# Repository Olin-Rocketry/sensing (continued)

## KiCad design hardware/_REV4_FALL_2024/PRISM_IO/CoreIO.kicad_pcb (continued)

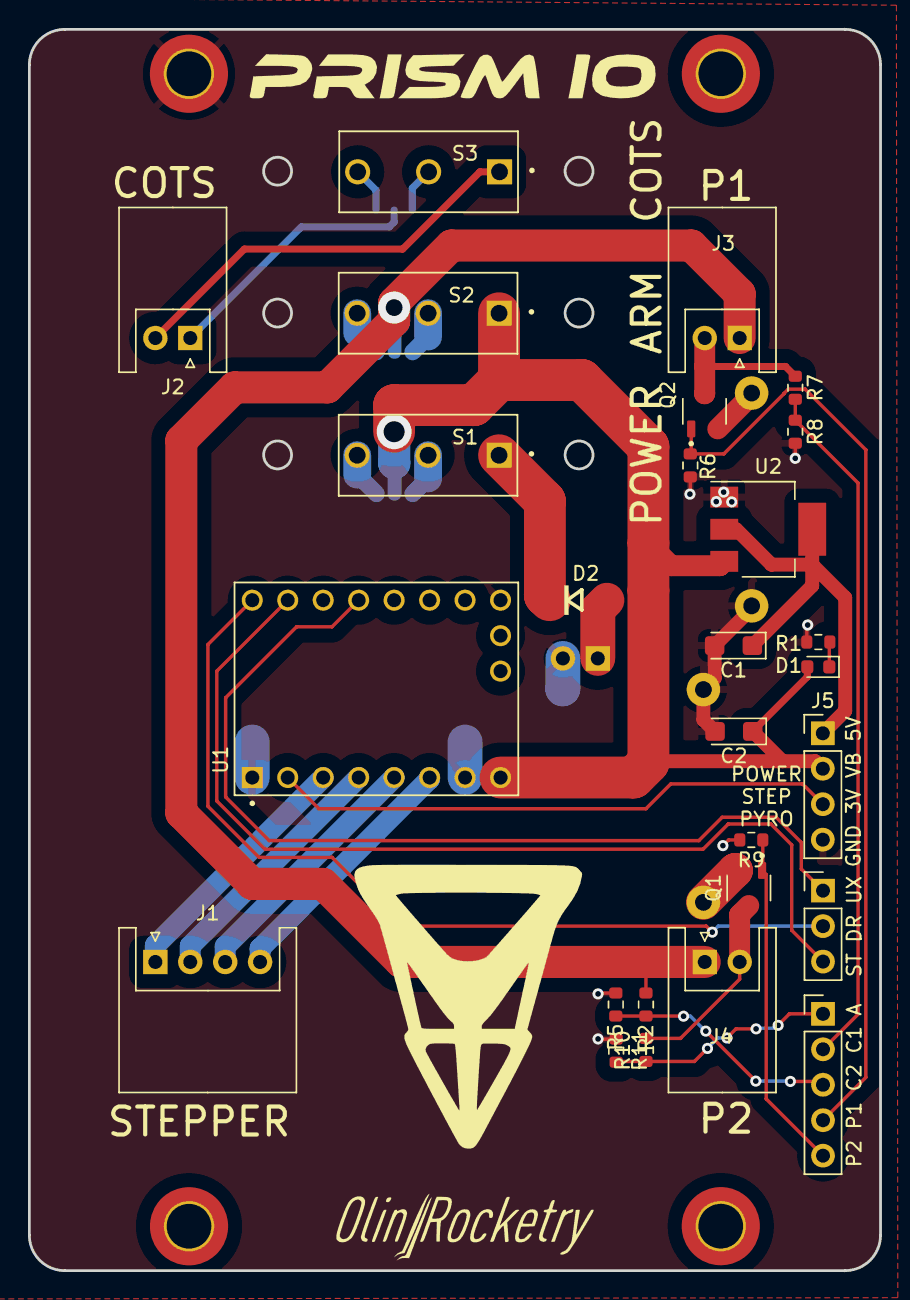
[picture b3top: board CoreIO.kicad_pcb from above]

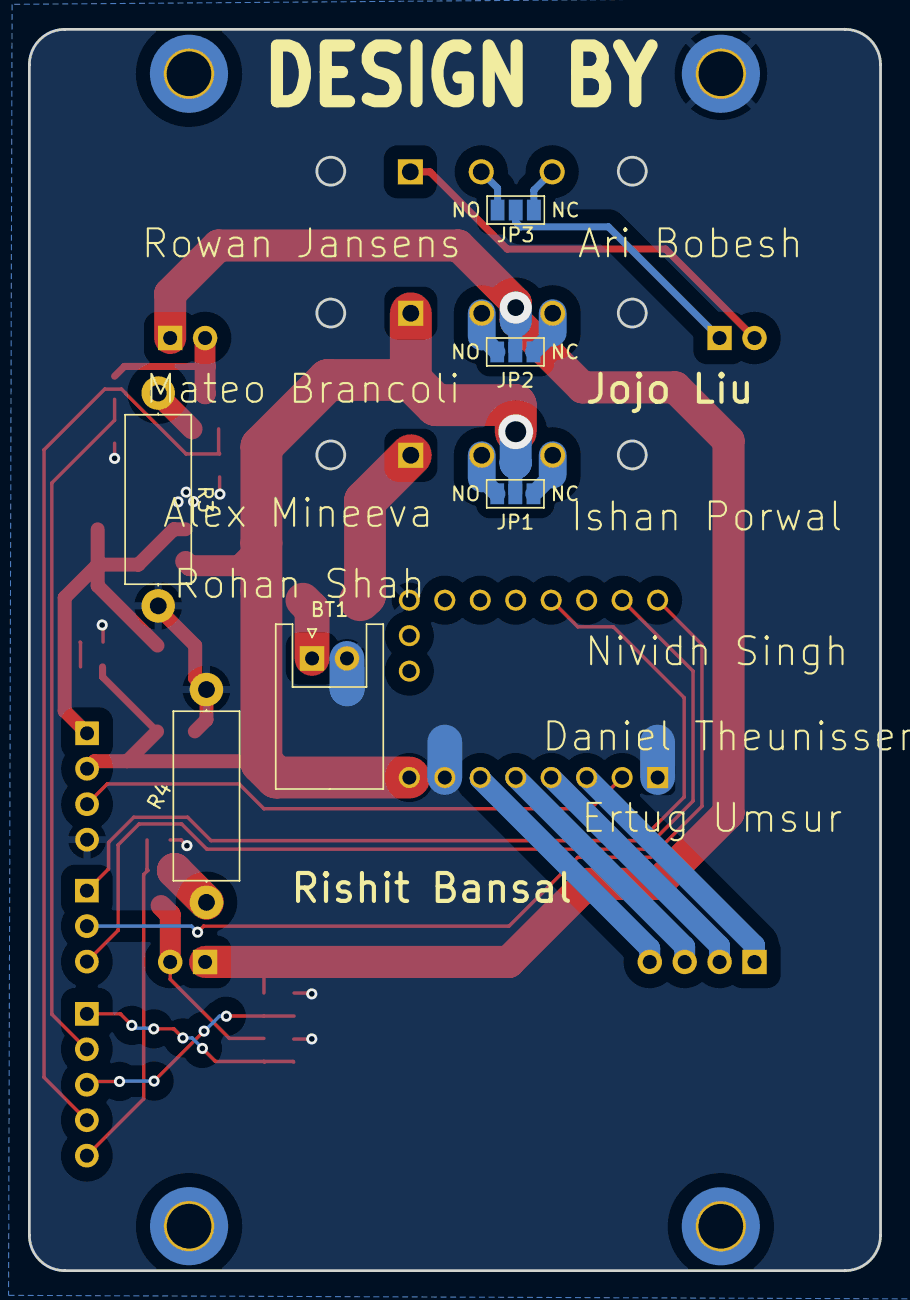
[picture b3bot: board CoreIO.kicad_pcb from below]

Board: 2 copper layers, 61.0 x 88.9 mm, 37 parts (6 on the bottom side), 32 nets.

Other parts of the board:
Pyro2: Conn_01x05_Socket; PinHeader_1x05_P2.54mm_Vertical
Stepper2: Conn_01x03_Socket; PinHeader_1x03_P2.54mm_Vertical

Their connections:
/ARM: Pyro2.3; also elsewhere on the board
/CONT 1: Pyro2.2; also elsewhere on the board
/CONT 2: Pyro2.1; also elsewhere on the board
/DIR: Stepper2.2; also elsewhere on the board
/PYRO 1: Pyro2.4; also elsewhere on the board
/PYRO 2: Pyro2.5; also elsewhere on the board
/STEP: Stepper2.3; also elsewhere on the board
/UART: Stepper2.1; also elsewhere on the board

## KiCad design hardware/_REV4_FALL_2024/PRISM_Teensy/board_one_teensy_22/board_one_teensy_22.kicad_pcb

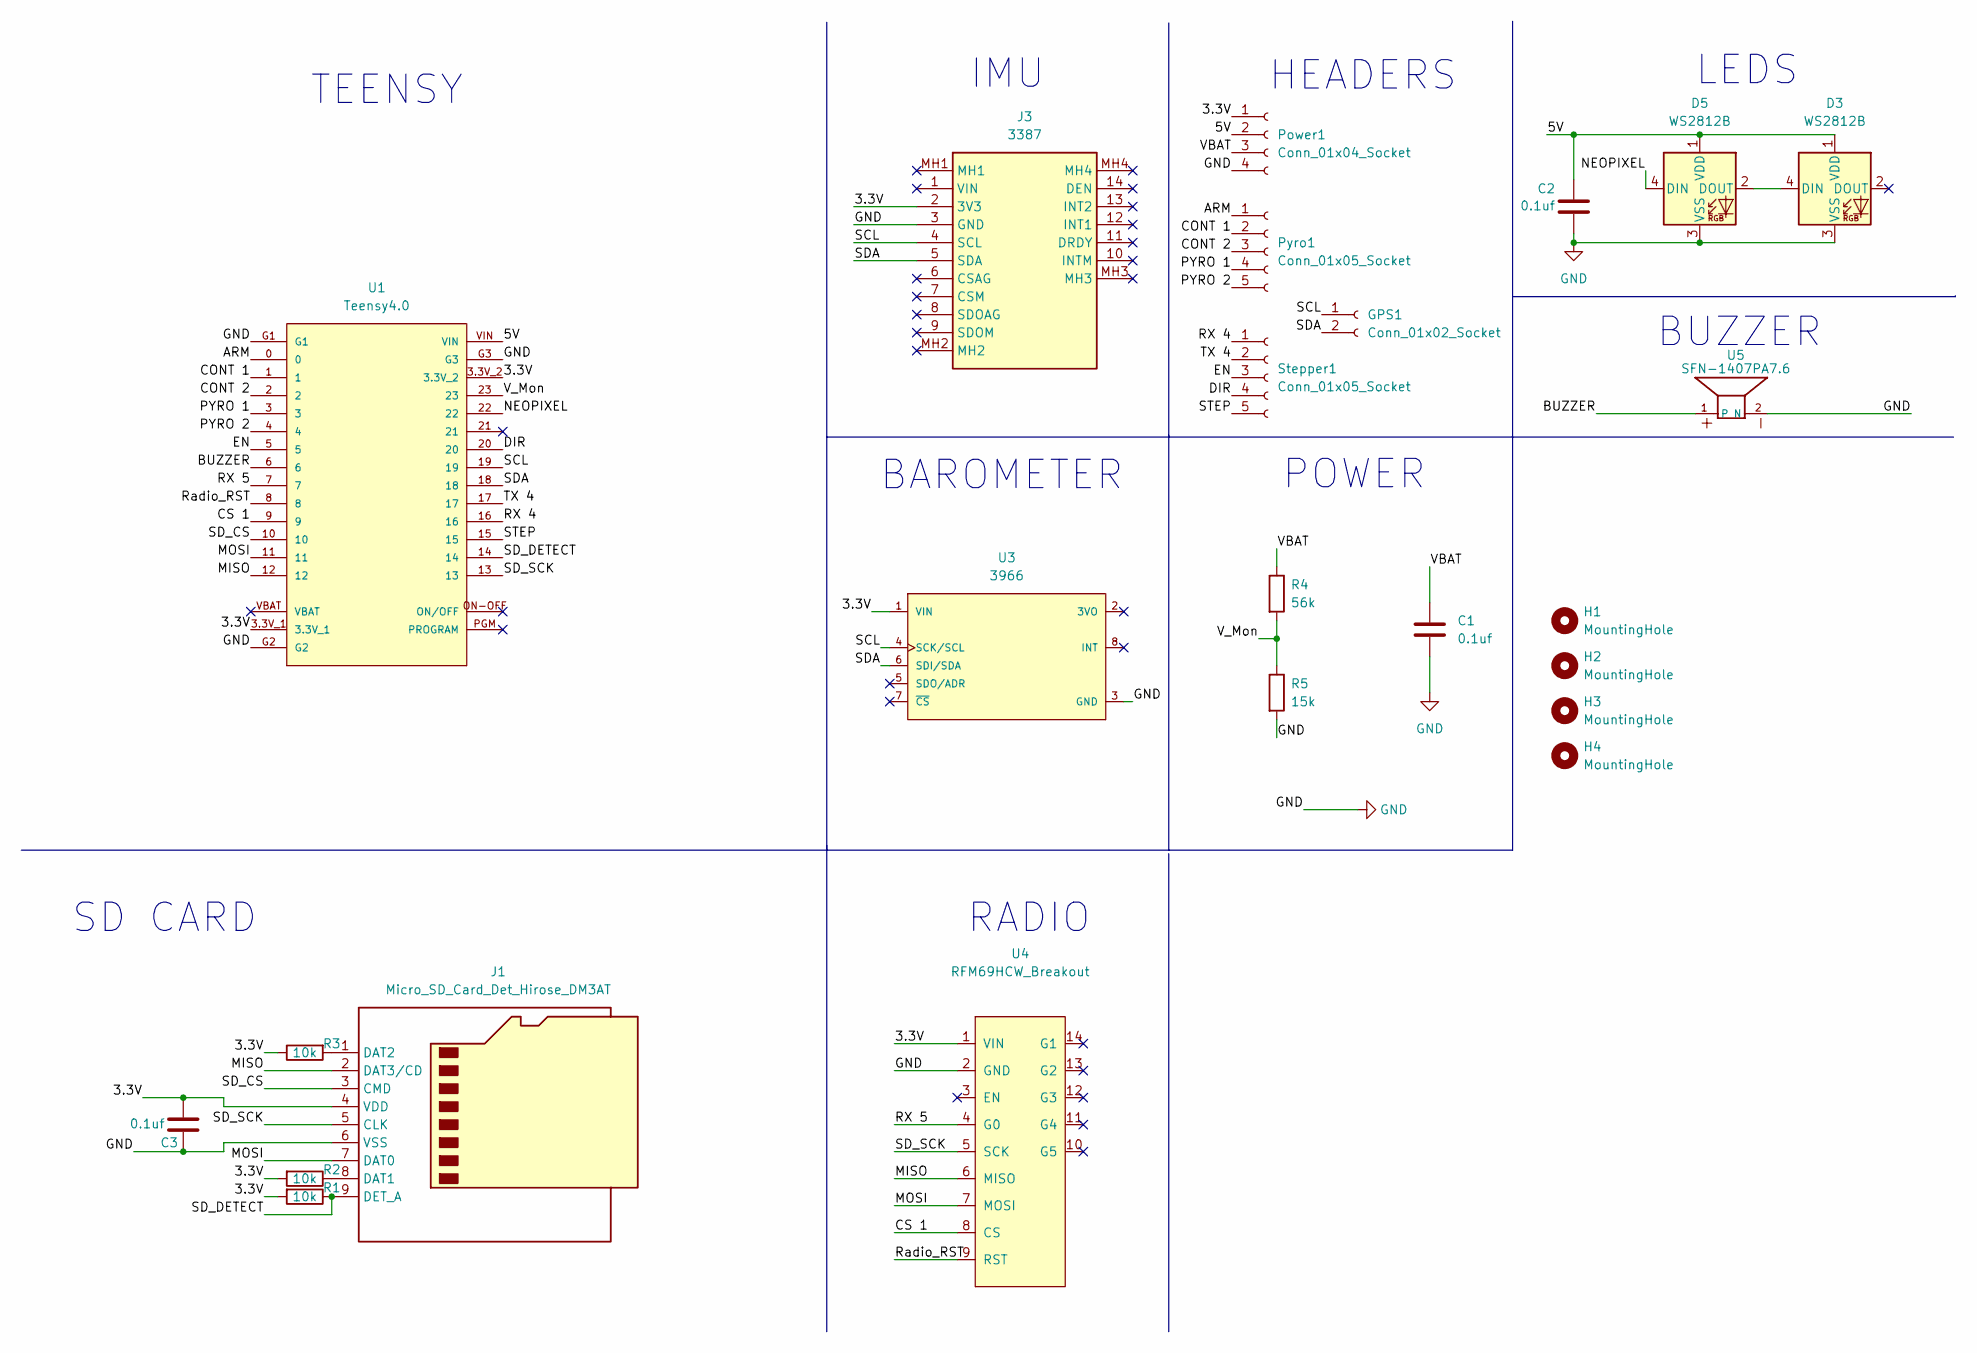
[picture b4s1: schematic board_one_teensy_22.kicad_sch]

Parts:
C1, C2, C3: 0.1uf; C_0603_1608Metric
D3, D5: WS2812B
GPS1: Conn_01x02_Socket; PinHeader_1x02_P2.54mm_Vertical
H1, H2, H3, H4: MountingHole; MountingHole_3.2mm_M3_DIN965_Pad_TopBottom
J1: Micro_SD_Card_Det_Hirose_DM3AT; HRS_DM3CS-SF
J3: 3387; Manufacturer_Part_Number 3387
Power1: Conn_01x04_Socket; PinHeader_1x04_P2.54mm_Vertical
Pyro1: Conn_01x05_Socket; PinHeader_1x05_P2.54mm_Vertical
R1, R2, R3: 10k; R_0603_1608Metric
R4: 56k; R_0603_1608Metric
R5: 15k; R_0603_1608Metric
Stepper1: Conn_01x05_Socket; PinHeader_1x05_P2.54mm_Vertical
U1: Teensy4.0; MODULE_DEV-15583
U3: 3966; Adafruit_Industries-3966-MFG; mouser part number 485-3966; digikey description BMP388 - PRECISION BAROMETRIC PR
U4: RFM69HCW_Breakout
U5: SFN-1407PA7.6; PARTREV 31/03/20

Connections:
/3.3V: C3.2, J1.4 (VDD), J3.2 (3V3), Power1.1, R1.2, R2.2, R3.1, U1.3.3V_1, U1.3.3V_2, U3.1 (VIN), U4.1 (VIN)
/5V: C2.2, D3.1 (VDD), D5.1 (VDD), Power1.2, U1.VIN
/ARM: Pyro1.1, U1.0
/BUZZER: U1.6, U5.1
/CONT 1: Pyro1.2, U1.1
/CONT 2: Pyro1.3, U1.2
/CS 1: U1.9, U4.8 (CS)
/DIR: Stepper1.4, U1.20
/EN: Stepper1.3, U1.5
/MISO: J1.2 (DAT3/CD), U1.12, U4.6 (MISO)
/MOSI: J1.7 (DAT0), U1.11, U4.7 (MOSI)
/NEOPIXEL: D5.4 (DIN), U1.22
/PYRO 1: Pyro1.4, U1.3
/PYRO 2: Pyro1.5, U1.4
/RX 4: Stepper1.1, U1.16
/RX 5: U1.7, U4.4 (G0)
/Radio_RST: U1.8, U4.9 (RST)
/SCL: GPS1.1, J3.4 (SCL), U1.19, U3.4 (SCK/SCL)
/SDA: GPS1.2, J3.5 (SDA), U1.18, U3.6 (SDI/SDA)
/SD_CS: J1.3 (CMD), U1.10
/SD_DETECT: J1.9 (DET_A), R1.1, U1.14
/SD_SCK: J1.5 (CLK), U1.13, U4.5 (SCK)
/STEP: Stepper1.5, U1.15
/TX 4: Stepper1.2, U1.17
/VBAT: C1.1, Power1.3, R4.1
/V_Mon: R4.2, R5.1, U1.23
GND: C1.2, C2.1, C3.1, D3.3 (VSS), D5.3 (VSS), J1.6 (VSS), J3.3 (GND), Power1.4, R5.2, U1.G1, U1.G2, U1.G3, U3.3 (GND), U4.2 (GND), U5.2 (N)
unnamed: D3.4 (DIN), D5.2 (DOUT)
unnamed: J1.8 (DAT1), R2.1
unnamed: J1.1 (DAT2), R3.2

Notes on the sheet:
BUZZER
TEENSY
HEADERS
SD CARD
POWER
LEDS
IMU
BAROMETER
RADIO

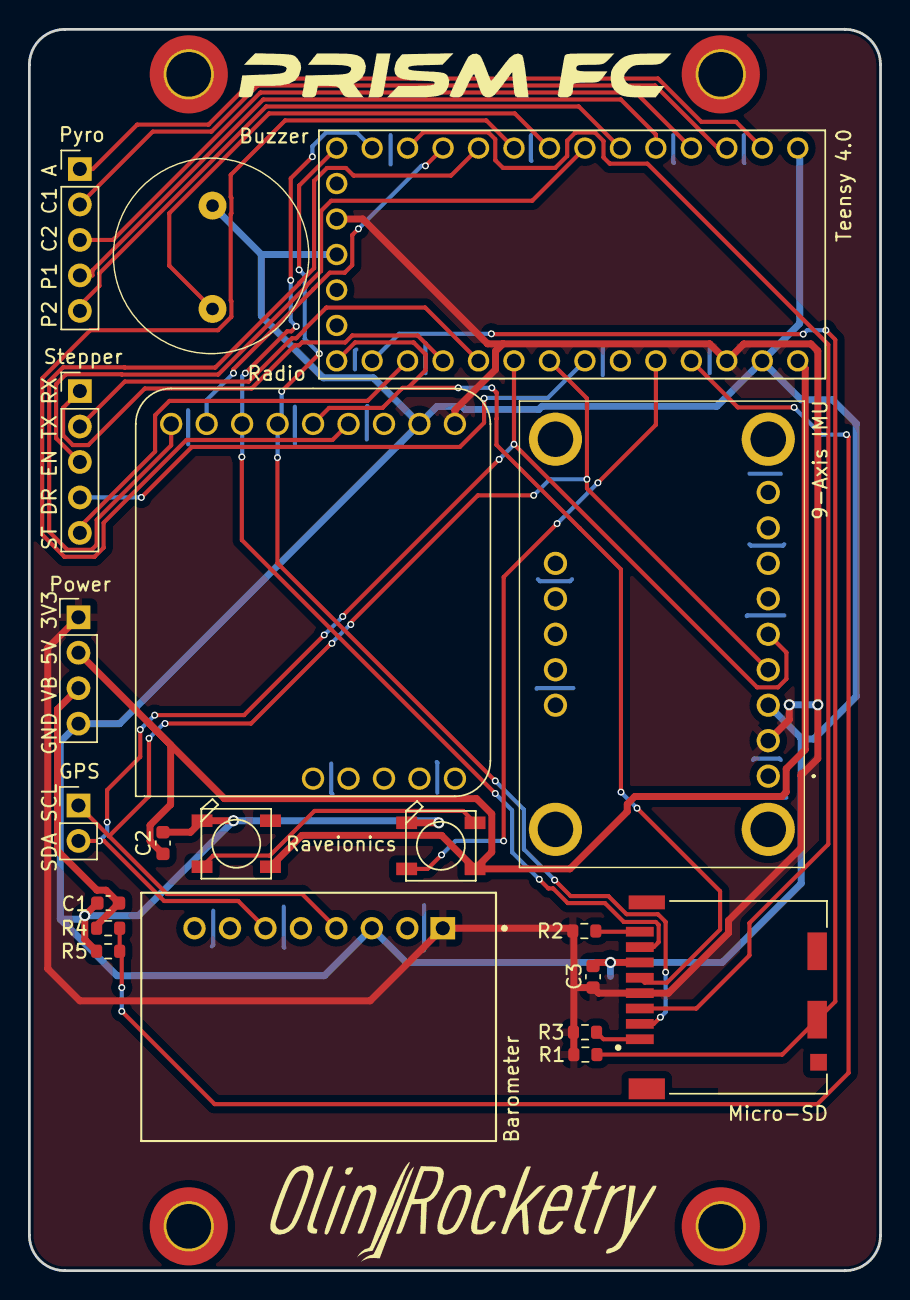
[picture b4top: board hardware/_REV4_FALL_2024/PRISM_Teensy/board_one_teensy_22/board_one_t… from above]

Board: 2 copper layers, 61.0 x 88.9 mm, 24 parts (0 on the bottom side), 30 nets.

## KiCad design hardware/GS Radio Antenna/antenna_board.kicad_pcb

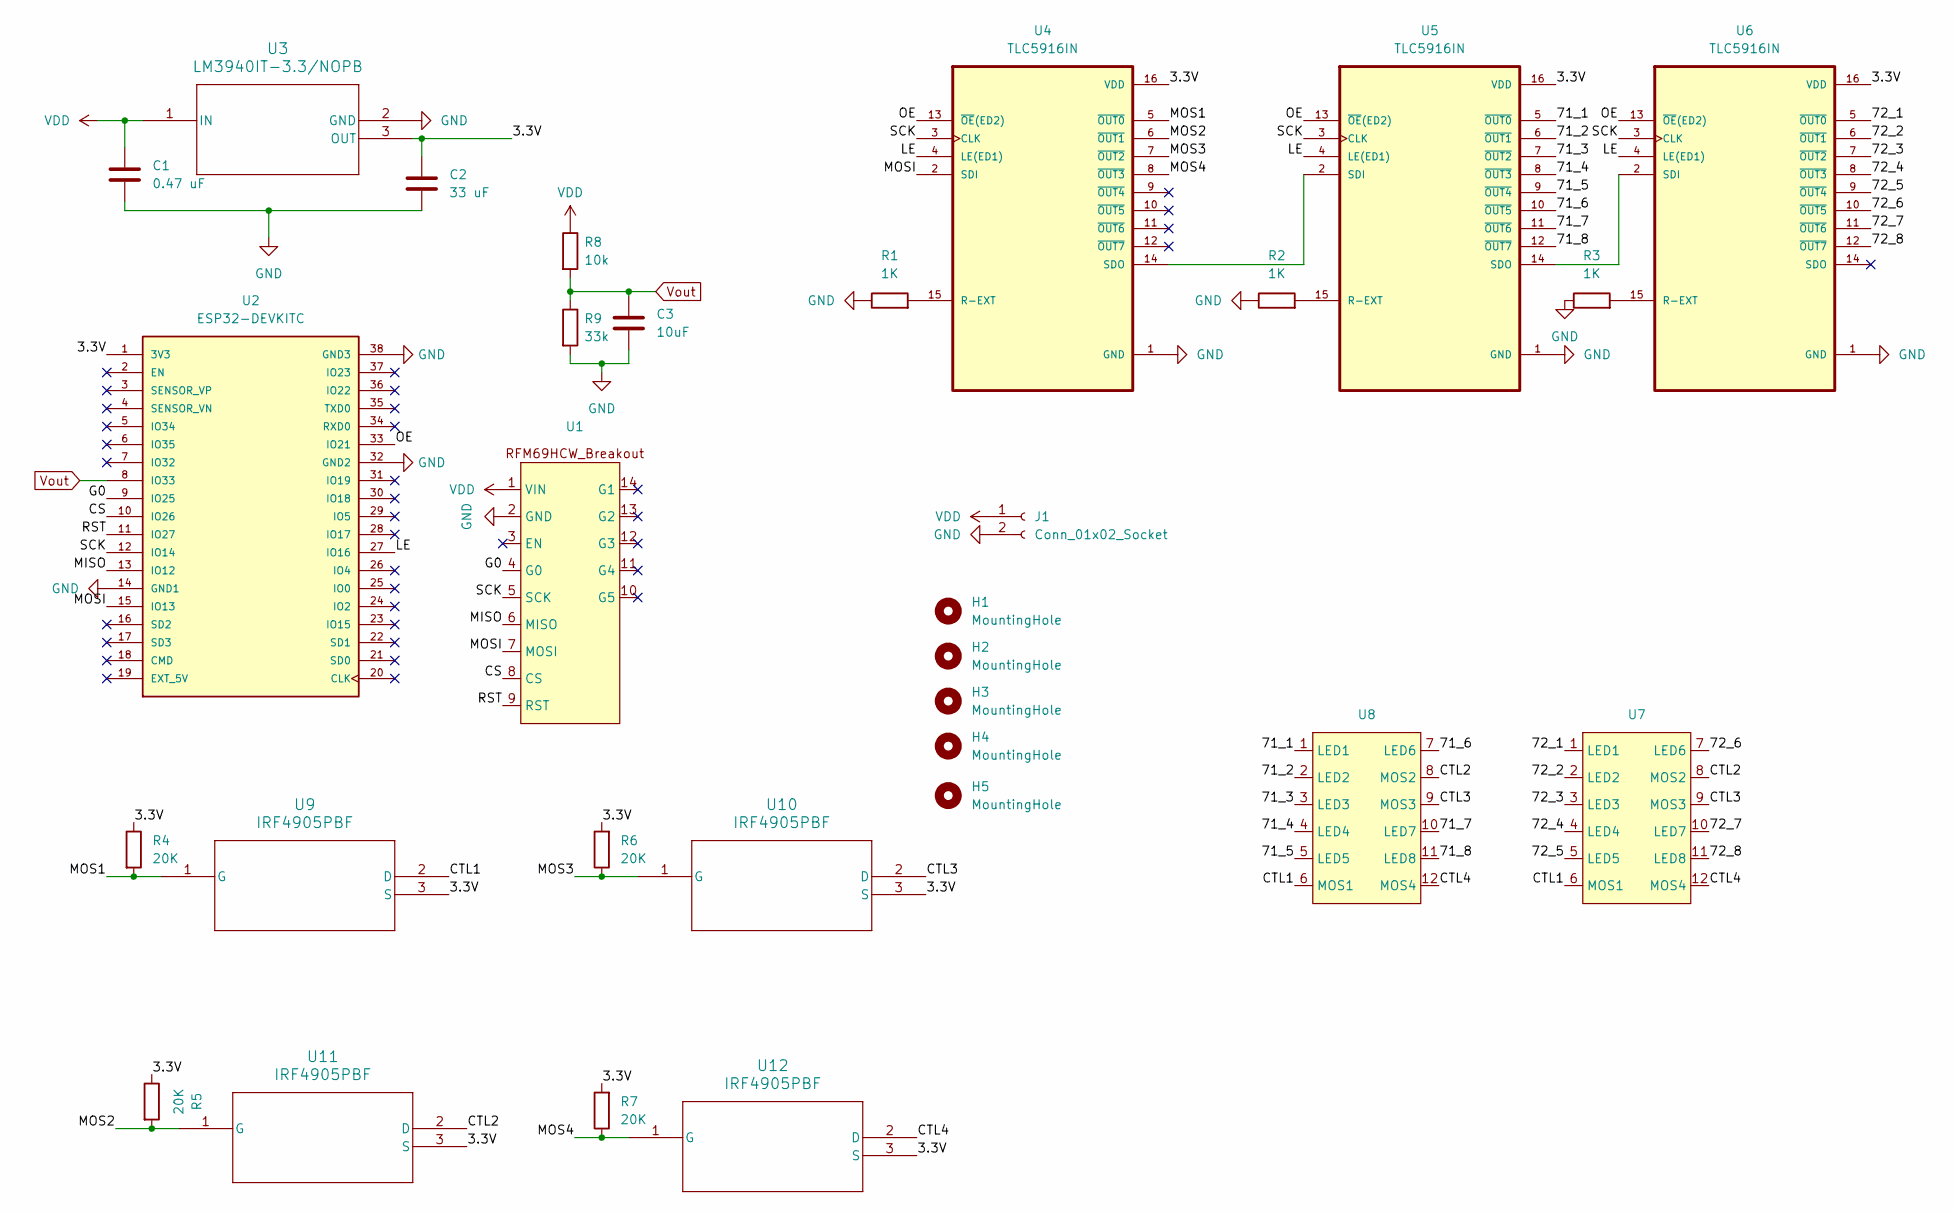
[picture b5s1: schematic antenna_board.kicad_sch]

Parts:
C1: 0.47 uF; C_0603_1608Metric_Pad1.08x0.95mm_HandSolder
C2: 33 uF; C_0805_2012Metric_Pad1.18x1.45mm_HandSolder
C3: 10uF; C_0603_1608Metric_Pad1.08x0.95mm_HandSolder
H1, H2, H3, H4, H5: MountingHole; MountingHole_3.2mm_M3_DIN965_Pad_TopBottom
J1: Conn_01x02_Socket; PinSocket_1x02_P2.54mm_Vertical
R1, R2, R3: 1K; R_0603_1608Metric_Pad0.98x0.95mm_HandSolder
R4, R5, R6, R7: 20K; R_0603_1608Metric_Pad0.98x0.95mm_HandSolder
R8: 10k; R_0603_1608Metric_Pad0.98x0.95mm_HandSolder
R9: 33k; R_0603_1608Metric_Pad0.98x0.95mm_HandSolder
U1: RFM69HCW_Breakout
U2: ESP32-DEVKITC; MODULE_ESP32-DEVKITC; PARTREV N/A
U3: LM3940IT-3.3/NOPB; LM3940IT
U4, U5, U6: TLC5916IN; DigiKey_Part_Number 296-24383-5-ND
U7, U8: Seven_Segment_Display
U9, U10, U11, U12: IRF4905PBF; PG-TO220-3_INF

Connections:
/3.3V: C2.1, R4.1, R5.1, R6.2, R7.2, U2.1 (3V3), U3.3 (OUT), U4.16 (VDD), U5.16 (VDD), U6.16 (VDD), U9.3 (S), U10.3 (S), U11.3 (S), U12.3 (S)
/71_1: U5.5 (~OUT0), U8.1 (LED1)
/71_2: U5.6 (~OUT1), U8.2 (LED2)
/71_3: U5.7 (~OUT2), U8.3 (LED3)
/71_4: U5.8 (~OUT3), U8.4 (LED4)
/71_5: U5.9 (~OUT4), U8.5 (LED5)
/71_6: U5.10 (~OUT5), U8.7 (LED6)
/71_7: U5.11 (~OUT6), U8.10 (LED7)
/71_8: U5.12 (~OUT7), U8.11 (LED8)
/72_1: U6.5 (~OUT0), U7.1 (LED1)
/72_2: U6.6 (~OUT1), U7.2 (LED2)
/72_3: U6.7 (~OUT2), U7.3 (LED3)
/72_4: U6.8 (~OUT3), U7.4 (LED4)
/72_5: U6.9 (~OUT4), U7.5 (LED5)
/72_6: U6.10 (~OUT5), U7.7 (LED6)
/72_7: U6.11 (~OUT6), U7.10 (LED7)
/72_8: U6.12 (~OUT7), U7.11 (LED8)
/CS: U1.8 (CS), U2.10 (IO26)
/CTL1: U7.6 (MOS1), U8.6 (MOS1), U9.2 (D)
/CTL2: U7.8 (MOS2), U8.8 (MOS2), U11.2 (D)
/CTL3: U7.9 (MOS3), U8.9 (MOS3), U10.2 (D)
/CTL4: U7.12 (MOS4), U8.12 (MOS4), U12.2 (D)
/G0: U1.4 (G0), U2.9 (IO25)
/LE: U2.27 (IO16), U4.4 (LE(ED1)), U5.4 (LE(ED1)), U6.4 (LE(ED1))
/MISO: U1.6 (MISO), U2.13 (IO12)
/MOS1: R4.2, U4.5 (~OUT0), U9.1 (G)
/MOS2: R5.2, U4.6 (~OUT1), U11.1 (G)
/MOS3: R6.1, U4.7 (~OUT2), U10.1 (G)
/MOS4: R7.1, U4.8 (~OUT3), U12.1 (G)
/MOSI: U1.7 (MOSI), U2.15 (IO13), U4.2 (SDI)
/OE: U2.33 (IO21), U4.13 (~OE(ED2)), U5.13 (~OE(ED2)), U6.13 (~OE(ED2))
/RST: U1.9 (RST), U2.11 (IO27)
/SCK: U1.5 (SCK), U2.12 (IO14), U4.3 (CLK), U5.3 (CLK), U6.3 (CLK)
GND: C1.2, C2.2, C3.2, J1.2, R1.1, R2.1, R3.1, R9.2, U1.2 (GND), U2.14 (GND1), U2.32 (GND2), U2.38 (GND3), U3.2 (GND), U4.1 (GND), U5.1 (GND), U6.1 (GND)
unnamed: R1.2, U4.15 (R-EXT)
unnamed: U4.14 (SDO), U5.2 (SDI)
unnamed: R2.2, U5.15 (R-EXT)
unnamed: U5.14 (SDO), U6.2 (SDI)
unnamed: R3.2, U6.15 (R-EXT)
VDD: C1.1, J1.1, R8.1, U1.1 (VIN), U3.1 (IN)
Vout: C3.1, R8.2, R9.1, U2.8 (IO33)

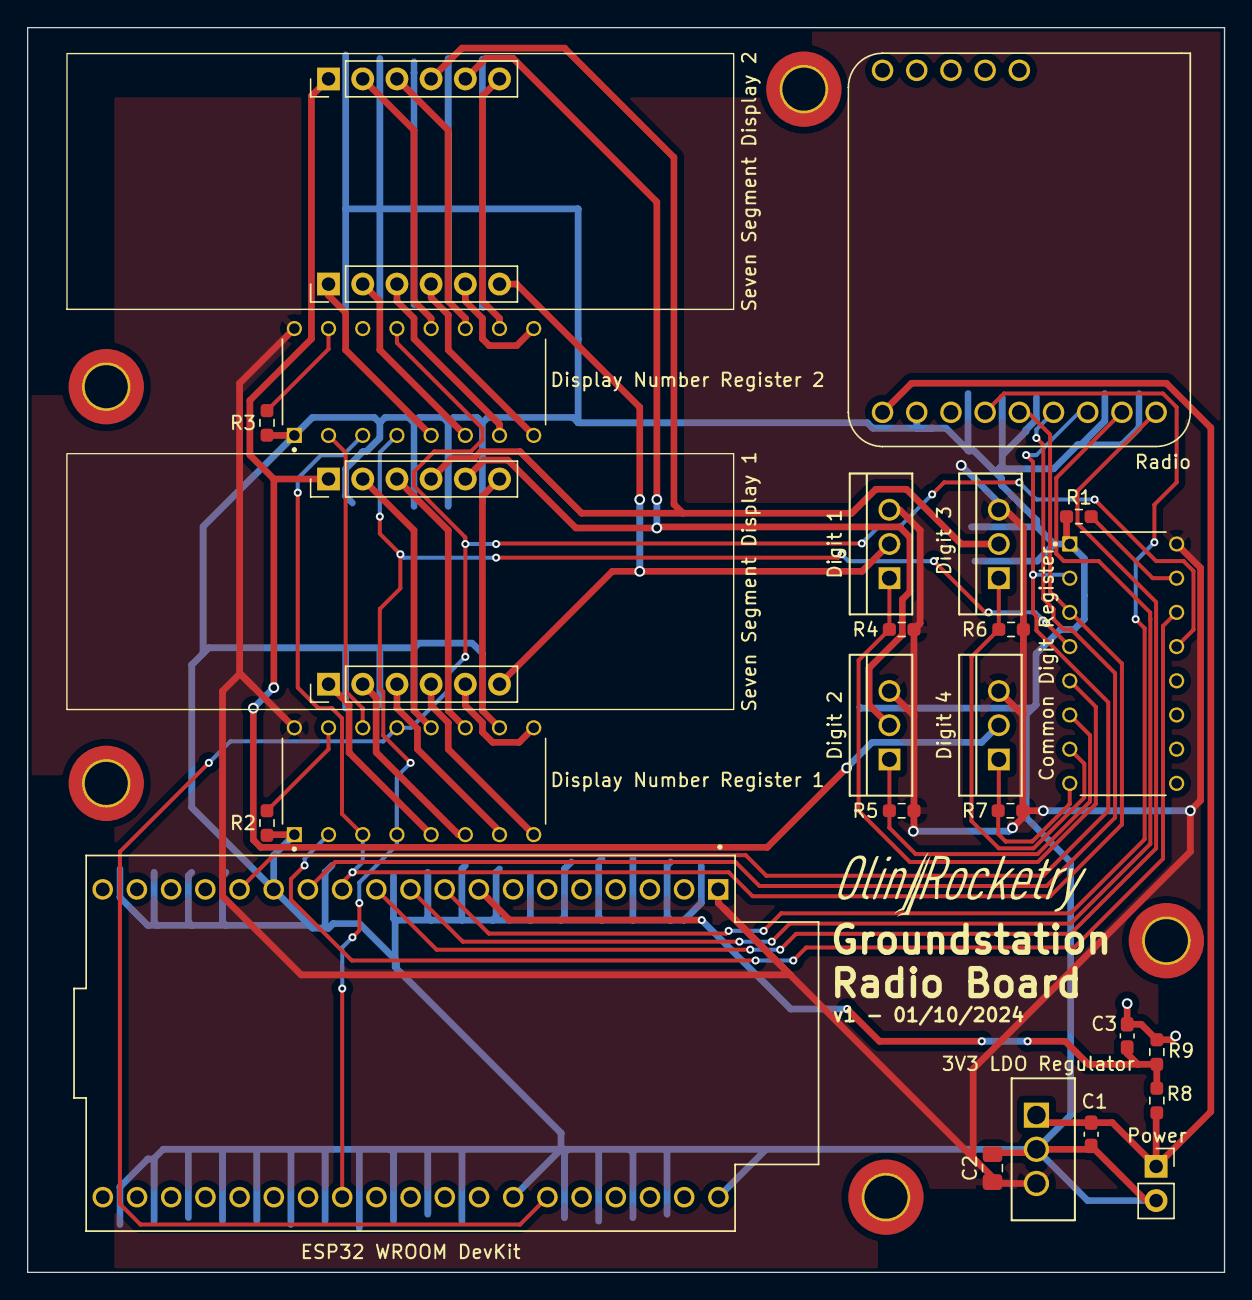
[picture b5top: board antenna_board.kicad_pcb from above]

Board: 2 copper layers, 88.9 x 92.5 mm, 30 parts (0 on the bottom side), 41 nets.

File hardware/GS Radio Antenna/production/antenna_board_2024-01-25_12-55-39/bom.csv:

Designator,Footprint,Quantity,Value,LCSC Part #
C1,0603,1,0.47 uF,
C2,0805,1,33 uF,
C3,0603,1,10uF,
"H1, H2, H3, H4, H5",MountingHole_3.2mm_M3_DIN965_Pad_TopBottom,5,MountingHole,
J1,PinSocket_1x02_P2.54mm_Vertical,1,Conn_01x02_Socket,
"R1, R2, R3",0603,3,1K,
"R4, R5, R6, R7",0603,4,20K,
R8,0603,1,10k,
R9,0603,1,33k,
U1,RFM69HCW_Breakout,1,~,
"U10, U11, U12, U9",PG-TO220-3_INF,4,IRF4905PBF,
U2,MODULE_ESP32-DEVKITC,1,ESP32-DEVKITC,
U3,LM3940IT,1,LM3940IT-3.3/NOPB,
"U4, U5, U6",TLC5916IN,3,TLC5916IN,
"U7, U8",Seven_Segment_Display,2,~,

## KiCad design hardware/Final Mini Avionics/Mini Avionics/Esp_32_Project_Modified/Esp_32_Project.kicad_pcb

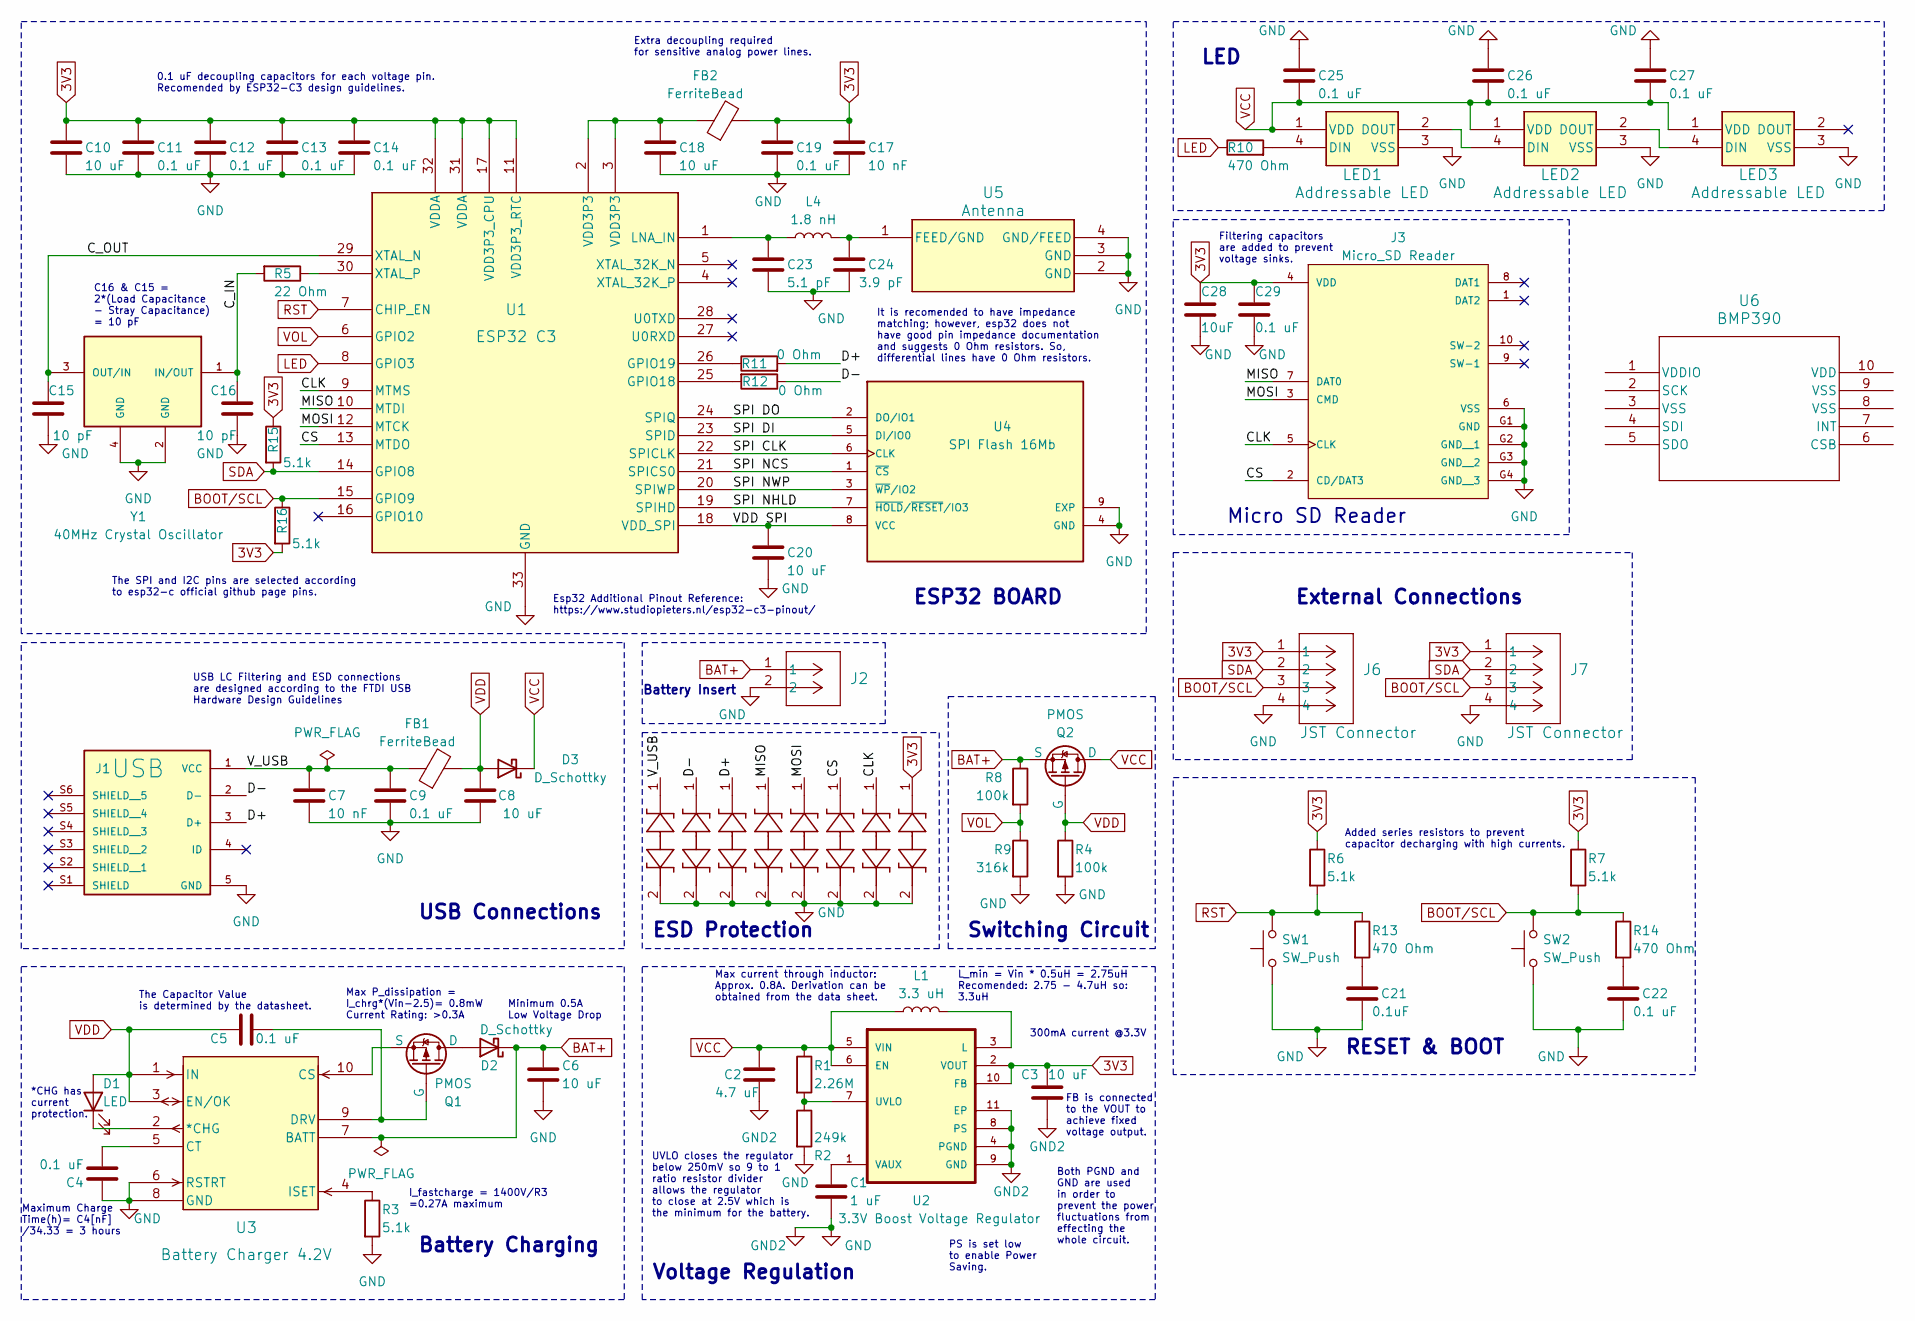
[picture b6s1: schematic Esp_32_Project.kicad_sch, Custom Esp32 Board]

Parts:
C1: 1 uF; C_0603_1608Metric_Pad1.08x0.95mm_HandSolder
C2: 4.7 uF; C_0603_1608Metric_Pad1.08x0.95mm_HandSolder
C3, C6, C8, C10, C18, C20: 10 uF; C_0603_1608Metric_Pad1.08x0.95mm_HandSolder
C4, C5, C9, C11, C12, C13, C14, C19, C22, C25, C26, C27, C29: 0.1 uF; C_0603_1608Metric_Pad1.08x0.95mm_HandSolder
C7, C17: 10 nF; C_0603_1608Metric_Pad1.08x0.95mm_HandSolder
C15, C16: 10 pF; C_0603_1608Metric_Pad1.08x0.95mm_HandSolder
C21: 0.1uF; C_0603_1608Metric_Pad1.08x0.95mm_HandSolder
C23: 5.1 pF; C_0603_1608Metric_Pad1.08x0.95mm_HandSolder
C24: 3.9 pF; C_0603_1608Metric_Pad1.08x0.95mm_HandSolder
C28: 10uF; C_0603_1608Metric_Pad1.08x0.95mm_HandSolder
CR1, CR2, CR3, CR4, CR5, CR6, CR7, CR8: ESD Protection; CR_SP3022_LTF
D1: LED; LED_0603_1608Metric_Pad1.05x0.95mm_HandSolder
D2, D3: D_Schottky; D_SMB_Handsoldering
FB1, FB2: FerriteBead; L_0201_0603Metric_Pad0.64x0.40mm_HandSolder
J1: USB; AMPHENOL_10118192-0002LF; PARTREV B
J2: Battery Connector; JST_XH_B2B-XH-A_1x02_P2.50mm_Vertical
J3: Micro_SD Reader; MicroSD Reader; PARTREV B2
J6, J7: JST Connector; JST_XH_B4B-XH-A_1x04_P2.50mm_Vertical
L1: 3.3 uH; L_0805_2012Metric_Pad1.05x1.20mm_HandSolder
L4: 1.8 nH; L_0402_1005Metric_Pad0.77x0.64mm_HandSolder
LED1, LED2, LED3: Addressable LED
Q1: PMOS; SOT-23-3
Q2: PMOS; SOT-323_SC-70_Handsoldering
R1: 2.26M; R_0603_1608Metric_Pad0.98x0.95mm_HandSolder
R2: 249k; R_0603_1608Metric_Pad0.98x0.95mm_HandSolder
R3, R6, R7, R15, R16: 5.1k; R_0603_1608Metric_Pad0.98x0.95mm_HandSolder
R4, R8: 100k; R_0603_1608Metric_Pad0.98x0.95mm_HandSolder
R5: 22 Ohm; R_0603_1608Metric_Pad0.98x0.95mm_HandSolder
R9: 316k; R_0603_1608Metric_Pad0.98x0.95mm_HandSolder
R10, R13, R14: 470 Ohm; R_0603_1608Metric_Pad0.98x0.95mm_HandSolder
R11, R12: 0 Ohm; R_0603_1608Metric_Pad0.98x0.95mm_HandSolder
SW1, SW2: SW_Push; Button
U1: ESP32 C3; QFN32_5X5_EXP
U2: 3.3V Boost Voltage Regulator; VREG_V62_16624-01YE
U3: Battery Charger 4.2V; 21-0061L_MXM
U4: SPI Flash 16Mb; IC_W25Q16JVUXIQ_TR; PARTREV H; DigiKey_Part_Number 256-W25Q16JVUXIQTR-ND
U5: Antenna; 2450AT18D0100E_JOT
U6: BMP390; LGA10_BMP390_BOS
Y1: 40MHz Crystal Oscillator; XTAL_ECS-400-9-36B-CKY-TR; DigiKey_Part_Number XC3060TR-ND

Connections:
3V3: C3.1, C10.1, C11.1, C12.1, C13.1, C14.1, C17.1, C19.1, C28.1, C29.1, CR8.1, FB2.2, J3.4 (VDD), J6.1, J7.1, R6.1, R7.1, R15.1, R16.2, U1.11 (VDD3P3_RTC), U1.17 (VDD3P3_CPU), U1.31 (VDDA), U1.32 (VDDA), U2.2 (VOUT), U2.10 (FB)
/CLK: CR7.1, J3.5 (CLK), U1.9 (MTMS)
/CS: CR6.1, J3.2 (CD/DAT3), U1.13 (MTDO)
/C_IN: C16.1, R5.2, Y1.1 (IN/OUT)
/C_OUT: C15.1, U1.29 (XTAL_N), Y1.3 (OUT/IN)
/D+: CR3.1, J1.3 (D+), R11.2
/D-: CR2.1, J1.2 (D-), R12.1
/MISO: CR4.1, J3.7 (DAT0), U1.10 (MTDI)
/MOSI: CR5.1, J3.3 (CMD), U1.12 (MTCK)
/SPI CLK: U1.22 (SPICLK), U4.6 (CLK)
/SPI DI: U1.23 (SPID), U4.5 (DI/IO0)
/SPI DO: U1.24 (SPIQ), U4.2 (DO/IO1)
/SPI NCS: U1.21 (SPICS0), U4.1 (~CS)
/SPI NHLD: U1.19 (SPIHD), U4.7 (~HOLD/~RESET/IO3)
/SPI NWP: U1.20 (SPIWP), U4.3 (~WP/IO2)
/VDD SPI: C20.1, U1.18 (VDD_SPI), U4.8 (VCC)
/V_USB: C7.1, C9.1, CR1.1, FB1.1, J1.1 (VCC)
BAT+: C6.1, D2.1 (K), J2.1, Q2.3 (S), R8.1, U3.7 (BATT)
BOOT/SCL: J6.3, J7.3, R7.2, R14.1, R16.1, SW2.2, U1.15 (GPIO9)
GND: C1.2, C2.2, C3.2, C4.1, C6.2, C7.2, C8.1, C9.2, C10.2, C11.2, C12.2, C13.2, C14.2, C15.2, C16.2, C17.2, C18.2, C19.2, C20.2, C21.2, C22.2, C23.2, C24.2, C25.1, C26.1, C27.1, C28.2, C29.2, CR1.2, CR2.2, CR3.2, CR4.2, CR5.2, CR6.2, CR7.2, CR8.2, J1.5 (GND), J2.2, J3.6 (VSS), J3.G1 (GND), J3.G2 (GND__1), J3.G3 (GND__2), J3.G4 (GND__3), J6.4, J7.4, LED1.3 (VSS), LED2.3 (VSS), LED3.3 (VSS), R2.2, R3.2, R4.2, R9.2, SW1.1, SW2.1, U1.33 (GND), U2.4 (PGND), U2.8 (PS), U2.9 (GND), U2.11 (EP), U3.6 (RSTRT), U3.8 (GND), U4.4 (GND), U4.9 (EXP), U5.2 (GND), U5.3 (GND), U5.4 (GND/FEED), Y1.2 (GND), Y1.4 (GND)
LED: R10.1, U1.8 (GPIO3)
unnamed: C18.1, FB2.1, U1.2 (VDD3P3), U1.3 (VDD3P3)
unnamed: C21.1, R13.2
unnamed: C22.1, R14.2
unnamed: D1.1 (K), U3.2 (*CHG)
unnamed: D2.2 (A), Q1.1 (D)
unnamed: LED1.4 (DIN), R10.2
unnamed: LED1.2 (DOUT), LED2.4 (DIN)
unnamed: LED2.2 (DOUT), LED3.4 (DIN)
unnamed: C5.2, Q1.2 (G), U3.9 (DRV)
unnamed: Q1.3 (S), U3.10 (CS)
unnamed: R12.2, U1.25 (GPIO18)
unnamed: R11.1, U1.26 (GPIO19)
unnamed: C23.1, L4.1, U1.1 (LNA_IN)
unnamed: R5.1, U1.30 (XTAL_P)
unnamed: L1.2, U2.3 (L)
unnamed: R1.2, R2.1, U2.7 (UVLO)
unnamed: C1.1, U2.1 (VAUX)
unnamed: C4.2, U3.5 (CT)
unnamed: R3.1, U3.4 (ISET)
unnamed: C24.1, L4.2, U5.1 (FEED/GND)
RST: R6.2, R13.1, SW1.2, U1.7 (CHIP_EN)
SDA: J6.2, J7.2, R15.2, U1.14 (GPIO8)
VCC: C2.1, C25.2, C26.2, C27.2, D3.1 (K), L1.1, LED1.1 (VDD), LED2.1 (VDD), LED3.1 (VDD), Q2.1 (D), R1.1, U2.5 (VIN), U2.6 (EN)
VDD: C5.1, C8.2, D1.2 (A), D3.2 (A), FB1.2, Q2.2 (G), R4.1, U3.1 (IN), U3.3 (EN/OK)
VOL: R8.2, R9.1, U1.6 (GPIO2)

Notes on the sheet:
USB LC Filtering and ESD connections are designed according to the FTDI USB Hardware Design Guidelines
Battery Charging
FB is connected to the VOUT to achieve fixed voltage output.
Voltage Regulation
ESP32 BOARD
ESD Protection
Extra decoupling required for sensitive analog power lines.
Max P_dissipation = I_chrg*(Vin-2.5)= 0.8mW Current Rating: >0.3A
The SPI and I2C pins are selected according to esp32-c official github page pins.
Minimum 0.5A Low Voltage Drop
The Capacitor Value is determined by the datasheet.
L_min = Vin * 0.5uH = 2.75uH Recomended: 2.75 - 4.7uH so: 3.3uH
300mA current @3.3V
UVLO closes the regulator below 250mV so 9 to 1 ratio resistor divider allows the regulator to close at 2.5V which is the minimum for the battery.
Filtering capacitors are added to prevent voltage sinks.
Micro SD Reader
I_fastcharge = 1400V/R3 =0.27A maximum
Esp32 Additional Pinout Reference: https://www.studiopieters.nl/esp32-c3-pinout/
LED
It is recomended to have impedance matching; however, esp32 does not have good pin impedance documentation and suggests 0 Ohm resistors. So, differential lines have 0 Ohm resistors.
Both PGND and GND are used in order to prevent the power fluctuations from effecting the whole circuit.
RESET & BOOT
*CHG has current protection.
PS is set low to enable Power Saving.
External Connections
Max current through inductor: Approx. 0.8A. Derivation can be obtained from the data sheet.
Battery Insert
0.1 uF decoupling capacitors for each voltage pin. Recomended by ESP32-C3 design guidelines.
USB Connections
C16 & C15 = 2*(Load Capacitance - Stray Capacitance) = 10 pF
Maximum Charge Time(h)= C4[nF] /34.33 = 3 hours
Switching Circuit
Added series resistors to prevent capacitor decharging with high currents.

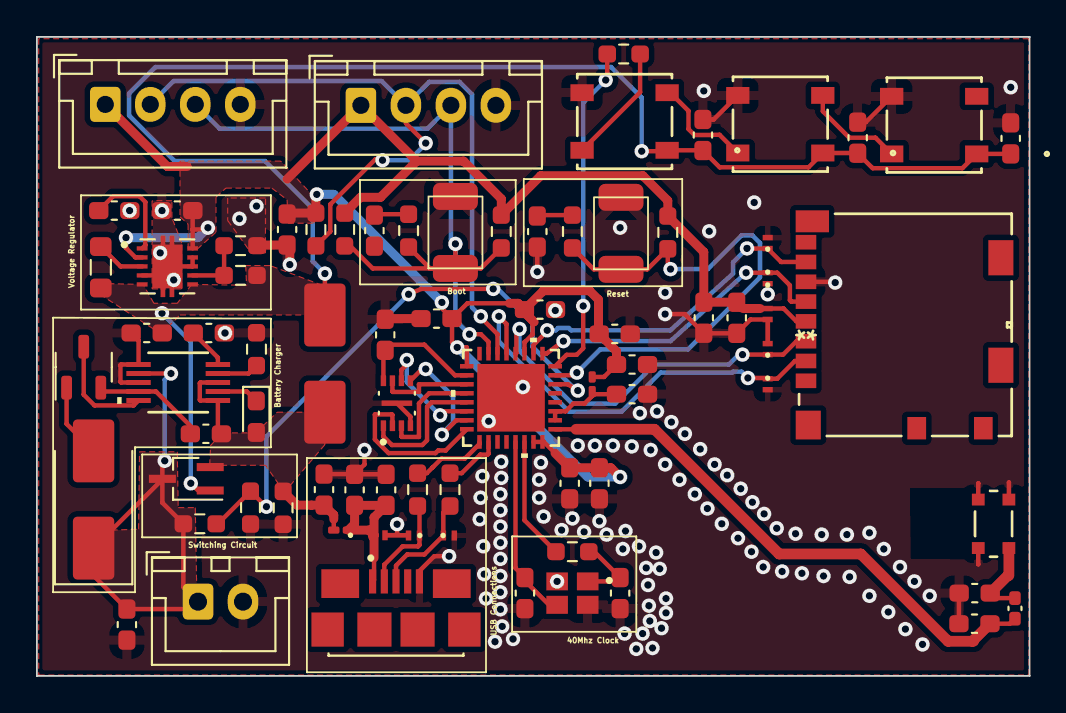
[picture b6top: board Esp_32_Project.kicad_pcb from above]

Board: 2 copper layers, 55.1 x 35.5 mm, 78 parts (0 on the bottom side), 46 nets.
